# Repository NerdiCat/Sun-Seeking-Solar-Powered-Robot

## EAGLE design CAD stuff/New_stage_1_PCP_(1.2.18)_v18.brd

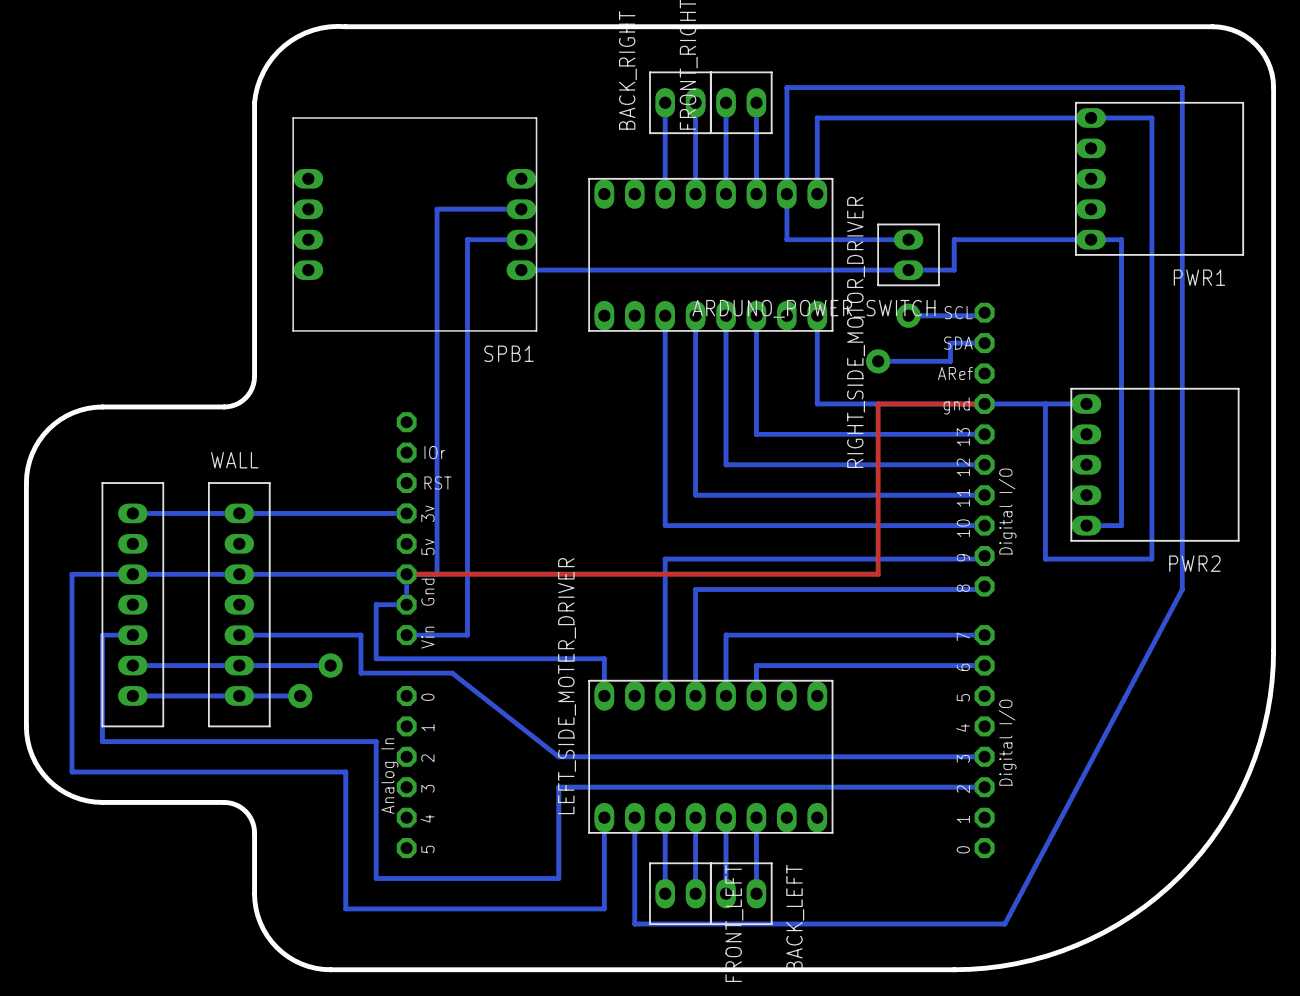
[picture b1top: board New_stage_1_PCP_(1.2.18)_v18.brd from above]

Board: 2 copper layers, 104.1 x 78.8 mm, 13 parts (0 on the bottom side), 27 nets.

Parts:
ARDUNO_POWER_SWITCH: MOTOR_OUTPUT_PINS
BACK_LEFT: MOTOR_OUTPUT_PINS
BACK_RIGHT: MOTOR_OUTPUT_PINS
CLIFF: DIST_SENS_OUTPUTPINS; DISTANCE_SENS_OUT
FRONT_LEFT: MOTOR_OUTPUT_PINS
FRONT_RIGHT: MOTOR_OUTPUT_PINS
LEFT_SIDE_MOTER_DRIVER: MOTOR_DRIVER
PWR1, PWR2: MICRO-USB_ADAPTER
RIGHT_SIDE_MOTOR_DRIVER: MOTOR_DRIVER
SPB1: SOFT-POWER_BUTTON; ADAFRUIT-SOFT-POWER-BUTTON_FOOTPRINT
U2: ARDUINOR3-BPLACE
WALL: DIST_SENS_OUTPUTPINS; DISTANCE_SENS_OUT

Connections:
2V8: CLIFF.2, WALL.2
+3.3V: CLIFF.1, U2.3V, WALL.1
+5V: SPB1.6, U2.VIN
CLIFF_SHDN: CLIFF.5, U2.D2
GND: CLIFF.3, LEFT_SIDE_MOTER_DRIVER.1, LEFT_SIDE_MOTER_DRIVER.9, PWR1.5, PWR2.5, RIGHT_SIDE_MOTOR_DRIVER.1, RIGHT_SIDE_MOTOR_DRIVER.9, SPB1.7, U2.GND, U2.GND1, U2.GND2, WALL.3
MPWR: ARDUNO_POWER_SWITCH.2, LEFT_SIDE_MOTER_DRIVER.2, RIGHT_SIDE_MOTOR_DRIVER.2
unnamed: FRONT_RIGHT.2, RIGHT_SIDE_MOTOR_DRIVER.3
unnamed: FRONT_RIGHT.1, RIGHT_SIDE_MOTOR_DRIVER.4
unnamed: BACK_RIGHT.2, RIGHT_SIDE_MOTOR_DRIVER.5
unnamed: BACK_RIGHT.1, RIGHT_SIDE_MOTOR_DRIVER.6
unnamed: FRONT_LEFT.2, LEFT_SIDE_MOTER_DRIVER.3
unnamed: FRONT_LEFT.1, LEFT_SIDE_MOTER_DRIVER.4
unnamed: BACK_LEFT.2, LEFT_SIDE_MOTER_DRIVER.5
unnamed: BACK_LEFT.1, LEFT_SIDE_MOTER_DRIVER.6
unnamed: RIGHT_SIDE_MOTOR_DRIVER.11, U2.D13
unnamed: RIGHT_SIDE_MOTOR_DRIVER.12, U2.D12
unnamed: RIGHT_SIDE_MOTOR_DRIVER.13, U2.D11
unnamed: RIGHT_SIDE_MOTOR_DRIVER.14, U2.D10
unnamed: LEFT_SIDE_MOTER_DRIVER.11, U2.D9
unnamed: LEFT_SIDE_MOTER_DRIVER.12, U2.D8
unnamed: LEFT_SIDE_MOTER_DRIVER.13, U2.D7
unnamed: LEFT_SIDE_MOTER_DRIVER.14, U2.D6
PWR_IN_5V: ARDUNO_POWER_SWITCH.1, PWR1.1, PWR2.1, SPB1.5
SCL: CLIFF.6, U2.SCL, WALL.6
SDA: CLIFF.7, U2.SDA, WALL.7
VMM: LEFT_SIDE_MOTER_DRIVER.10, RIGHT_SIDE_MOTOR_DRIVER.10
WALL_SHDN: U2.D3, WALL.5

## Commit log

2021-09-22 Adding everything
    I added all of my files for this project, don't know if I will be able to use folder sorting because otherwise this is gonna get messy
2021-09-22 changed to turning left
    changed main function to turn left instead of move forward
2021-09-22 Added cliff sensor
2021-09-23 worked on trouble shooting and improving the falling code
    note to self: need to deal with problem of sensor being also a color sensor
2021-09-24 added comments
    needed to do something and didn't have time to be productive so I added some comments to the code to clarify stuff
2021-09-27 trying to debug serial monitor
2021-09-28 calibrating and troubleshooting
2021-10-30 1st circuit diagram
    This is the circuit diagram I made during 11th grade for what this robot will eventually have
2022-01-04 added new code for adafruit tof sensor
    copied code from example. need to remove extranious code and modify to fit purpose
2022-01-05 modified falling code for new sensor
    set up the preexsisting falling code so that it works with the new sensor.
    next I should remove unnecessary comments
2022-01-10 moved bracket to new folder
2022-01-14 Update Sensor.ino
    added some of the setup code from the distance sensory library I am using and modified to work with 2 sensors instead of 3. Still need to add and modify the sensor functionality functions. (may repla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
2022-01-18 redid library code insertion and modification
    instead of trying to copy all of the useful library stuff, I copied everything and commented out the extraneous stuff
2022-01-19 experimenting
    messed around with some stuff to try and get the sensor code to work with the falling code but didn't have enough time to really get into it
2022-01-19 got sensor readings working
2022-01-19 got rid of some old comments
    removed comments that were previous code commented out to tidy up the code
2022-01-24 Update NewMotorCode.ino
    accidentally added a space and decided doing this was simpler because it asked me to save changes and I didn't know what changes and at this point I might as well commit
2022-02-02 made custom devices for the circuit board
2022-02-03 added name and value
    added name and value to the symbols of some of the device libraries and also fixed the file types of some while at it
2022-02-03 flipped the + and - labels on the pins
2022-03-01 Update NewMotorCode.ino
    trouble shooting code with new board and something is interfearing with when I set at least pin 13 but likely the others to high and the multimeter is saying it isn't unless I only run that code
2022-03-04 troubleshooting
2022-03-28 trouble shooting
2022-05-12 Added delays
    the arduino can't handele the sudden drop in (current or voltage idk which) that comes from turning on 4 motors at once so I made it turn on 2 at a time with delays
2022-05-16 converted cliff sensor extender from fusion to pdf
2022-05-17 tried fixing current drop and falling balance (failed)
